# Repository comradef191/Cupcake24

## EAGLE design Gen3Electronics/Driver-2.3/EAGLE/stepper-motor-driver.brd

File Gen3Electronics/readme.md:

# About
The electronics within the final Cupcake24 build will be a modernised variant of the original Gen3 electronics, with the following changes made from the original files:

- PCB & Schematics ported to KiCAD 8.0
  - Reorganisation of Schematic to fit into one small page
  - Symbol locations adjusted to make values easier to read
  - Where possible, Schematic symbols swapped for KiCAD equivalents
  - Where possible, PCB footprints swapped for KiCAD equivalents
- PCB outline re-drawn and rounded-off
- PCB modified to run ground through the groundplane, rather than individual traces
- All traces, text, vias ect adjusted to be entirely metric (I.E: 0.3048mm traces (12mill) changed to 0.3mm traces)
- Silkscreen entirely overhauled, with information more clearly marked, text relocated & re-sized for improved readability, and information about Cupcake24 in an out-of-sight place (Generally, the rear of the PCB, or under a large component such as the SD reader)
- Some minor fixes to some traces not being run entirely in straight lines

# Electronics Status:

**RepRap Motherboard v1.2**
- [x] Converted to modern Eagle
- [x] Files Ported to KiCAD 8.0
- [x] Schematic modernised & cleaned-up
- [ ] PCB Modernised & cleaned-up
- [ ] Component sources designated; BoM Complete
- [ ] PCB Ordered
- [ ] PCB Assembled & Tested
- Comment: PCB mostly complete, some cleanup and tweaks to be done.

**Stepper Motor Driver v2.3**
- [x] Converted to modern Eagle
- [x] Files Ported to KiCAD 8.0
- [x] Schematic modernised & cleaned-up
- [x] PCB Modernised & cleaned-up
- [x] Component sources designated; BoM Complete
- [ ] PCB Ordered
- [ ] PCB Assembled & Tested

**Extruder Controller v2.2**
- [x] Converted to modern Eagle
- [x] Files Ported to KiCAD 8.0
- [ ] Schematic modernised & cleaned-up
- [ ] PCB Modernised & cleaned-up
- [ ] Component sources designated; BoM Complete
- [ ] PCB Ordered
- [ ] PCB Assembled & Tested

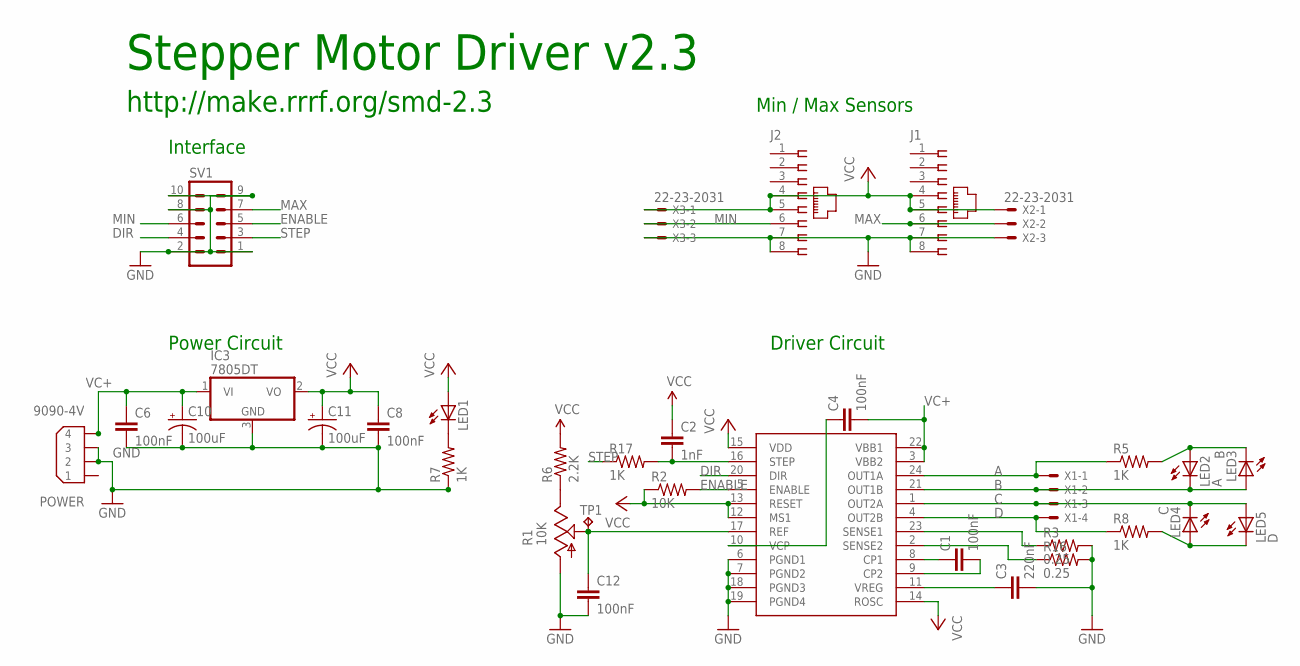
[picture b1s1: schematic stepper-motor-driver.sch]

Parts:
C1, C4, C12: 100nF; C1206
C2: 1nF; C1206K
C3: 220nF; C1206
C6, C8: 100nF; C1206K
C10, C11: 100uF; UD-10X10_NICHICON
DRIVER: A3982; SO24W
IC3: 7805DT; TO252
J1, J2: 520426-4
LED1: LEDCHIPLED_1206; CHIPLED_1206
LED2: A; CHIPLED_1206
LED3: B; CHIPLED_1206
LED4: C; CHIPLED_1206
LED5: D; CHIPLED_1206
POWER: 9090-4V
R1: 10K; B25P
R2: 10K; R1206
R3, R16: 0.25; R2512
R5, R7, R8, R17: 1K; R1206
R6: 2.2K; R1206
SV1: ML10
TP1: TPPAD1-13; P1-13
X1: KK-156-4
X2, X3: 22-23-2031

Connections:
A: DRIVER.24 (OUT1A), R5.1, X1.1
B: DRIVER.21 (OUT1B), LED2.C, LED3.A, X1.2
C: DRIVER.1 (OUT2A), LED4.C, LED5.A, X1.3
D: DRIVER.4 (OUT2B), R8.1, X1.4
DIR: DRIVER.20 (DIR), SV1.4
ENABLE: DRIVER.5 (ENABLE), R2.2, SV1.5
GND: C3.2, C6.2, C8.2, C10.-, C11.-, C12.2, DRIVER.6 (PGND1), DRIVER.7 (PGND2), DRIVER.18 (PGND3), DRIVER.19 (PGND4), IC3.3 (GND), J1.7, J1.8, J2.7, J2.8, POWER.2, POWER.3, R1.A, R3.2, R7.1, R16.2, SV1.1, SV1.2, SV1.8, SV1.9, SV1.10, X2.3, X3.3
MAX: J1.6, SV1.7, X2.2
MIN: J2.6, SV1.6, X3.2
unnamed: DRIVER.23 (SENSE1), R3.1
unnamed: DRIVER.2 (SENSE2), R16.1
unnamed: C1.1, DRIVER.8 (CP1)
unnamed: C1.2, DRIVER.9 (CP2)
unnamed: C3.1, DRIVER.11 (VREG)
unnamed: R1.E, R6.1
unnamed: C4.1, DRIVER.10 (VCP)
unnamed: LED1.C, R7.2
unnamed: LED2.A, LED3.C, R5.2
unnamed: LED4.A, LED5.C, R8.2
unnamed: C12.1, DRIVER.17 (REF), R1.S, TP1.1
unnamed: C2.2, DRIVER.16 (STEP), R17.2
STEP: R17.1, SV1.3
VC+: C4.2, C6.1, C10.+, DRIVER.3 (VBB2), DRIVER.22 (VBB1), IC3.1 (VI), POWER.4
VCC: C2.1, C8.1, C11.+, DRIVER.12 (MS1), DRIVER.13 (RESET), DRIVER.14 (ROSC), DRIVER.15 (VDD), IC3.2 (VO), J1.4, J1.5, J2.4, J2.5, LED1.A, R2.1, R6.2, X2.1, X3.1

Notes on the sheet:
Interface
Driver Circuit
Min / Max Sensors
Stepper Motor Driver v2.3
http://make.rrrf.org/smd-2.3
Power Circuit

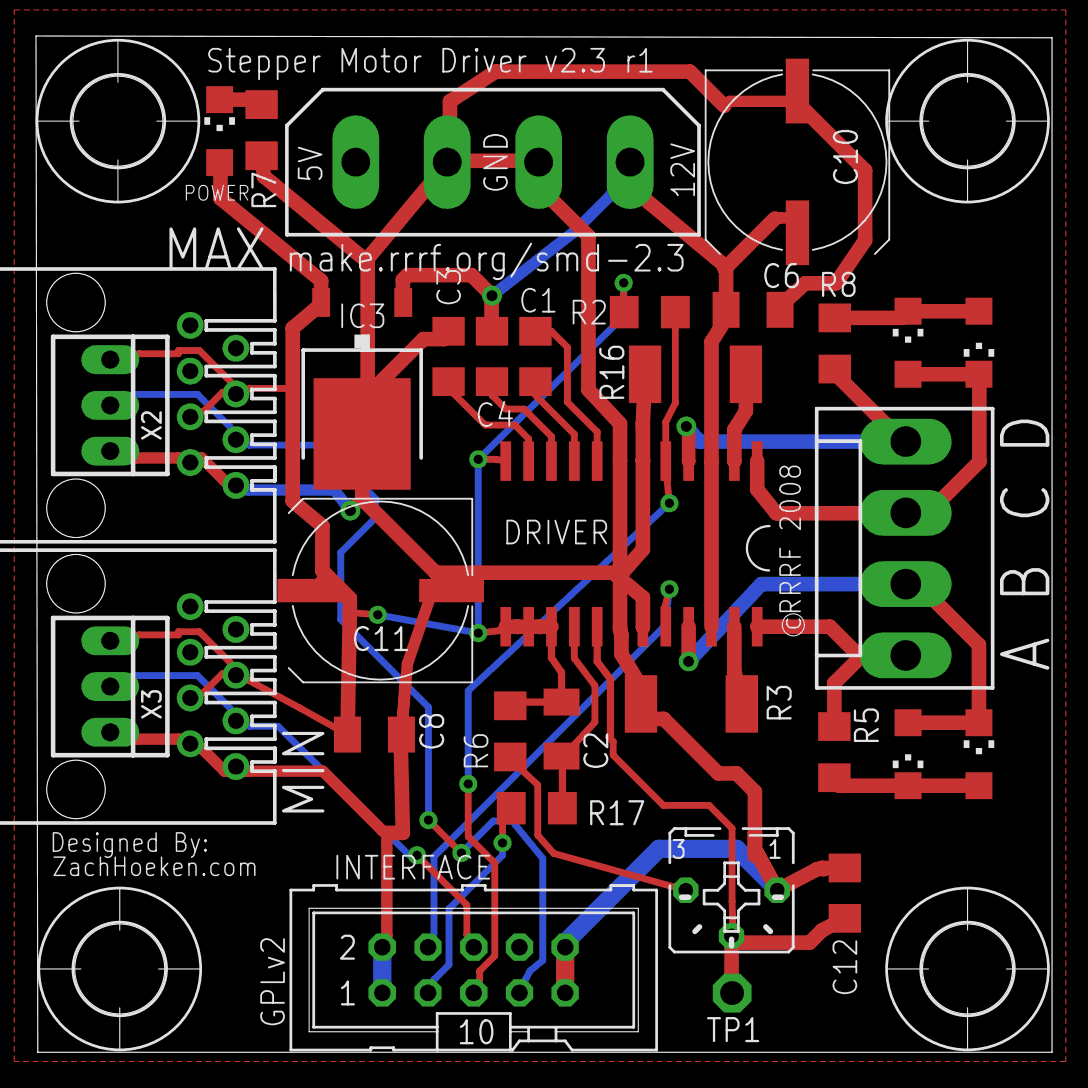
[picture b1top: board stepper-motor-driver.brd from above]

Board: 2 copper layers, 56.4 x 56.5 mm, 37 parts (0 on the bottom side), 24 nets.

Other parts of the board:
U$1, U$2, U$3, U$4: 5,0

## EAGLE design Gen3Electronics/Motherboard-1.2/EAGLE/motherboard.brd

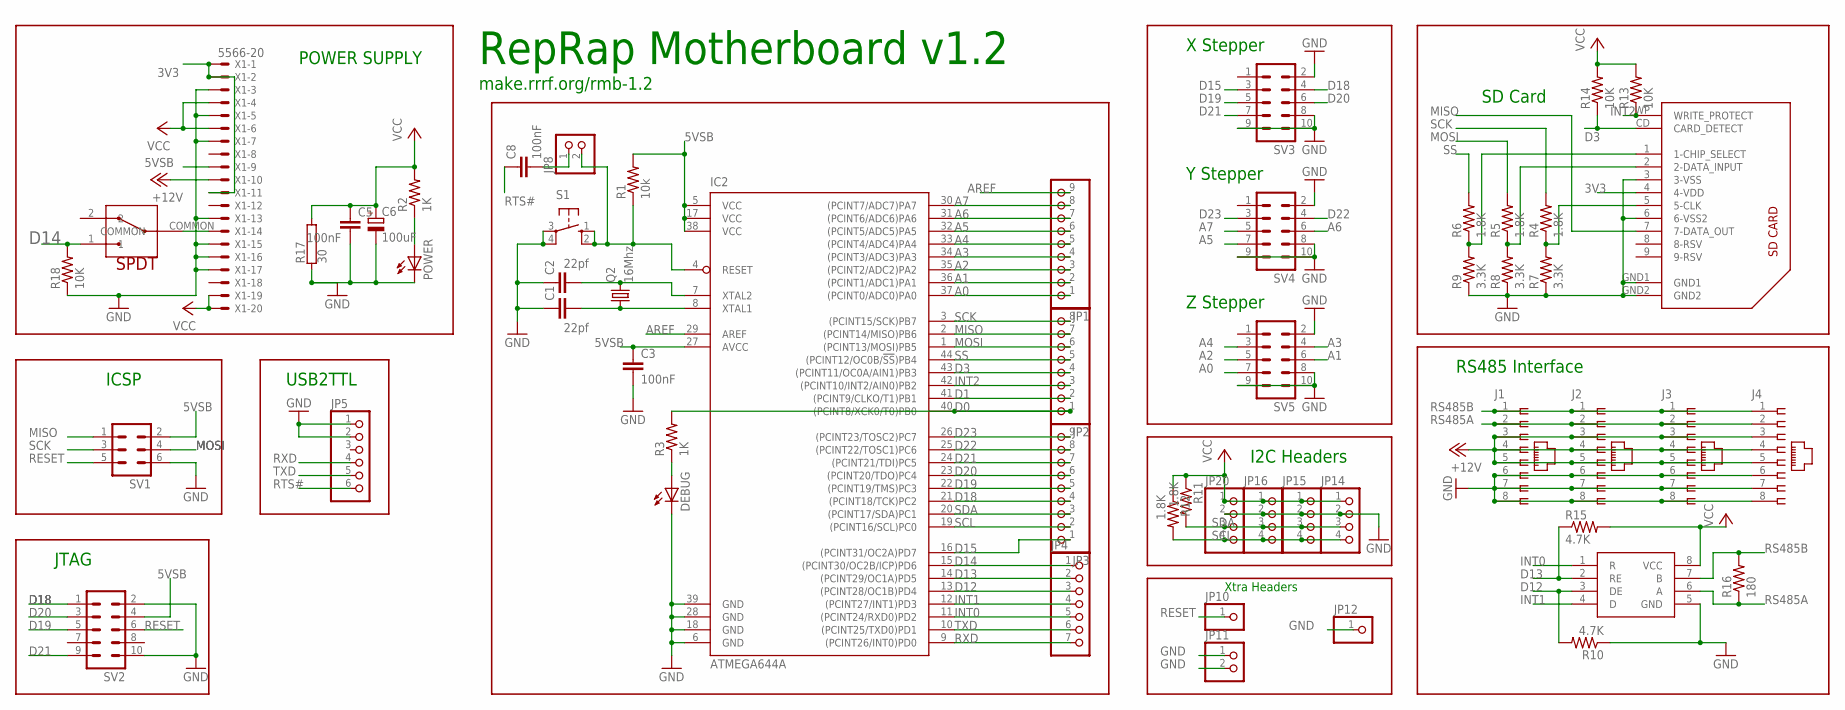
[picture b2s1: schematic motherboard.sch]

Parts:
C1, C2: 22pf; C1206
C3, C5, C8: 100nF; C1206
C6: 100uF; SANYO-OSCON_SMD_B6
DEBUG: LEDCHIPLED_1206; CHIPLED_1206
IC1: SN75176ASOIC; SO08
IC2: ATMEGA644A; TQFP44
J1, J2, J3, J4: 555164-1
JP1, JP3: PINHD-1X9; 1X09
JP2: PINHD-1X8; 1X08
JP4: PINHD-1X7; 1X07
JP5: PINHD-1X6; 1X06
JP8, JP11: PINHD-1X2; 1X02
JP10, JP12: PINHD-1X1; 1X01
JP14, JP15, JP16, JP20: PINHD-1X4; 1X04
POWER: LEDCHIPLED_1206; CHIPLED_1206
Q2: 16Mhz; HC49U-V
R1: 10k; R1206
R2, R3: 1K; R1206
R4, R5, R6, R11, R12: 1.8K; R1206
R7, R8, R9: 3.3K; R1206
R10, R15: 4.7K; R1206
R13, R14, R18: 10K; R1206
R16: 180; R1206
R17: 30; KH206-8
S1: 10-XX; B3F-10XX
SV1: ML6
SV2, SV3, SV4, SV5: ML10
U$2: SPDT; 10SP001
U$8: SDCARD; 3M-SDCARD
X1: 5566-20

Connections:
3V3: U$8.4 (4-VDD), X1.1, X1.2, X1.11
5VSB: C3.1, IC2.5 (VCC), IC2.17 (VCC), IC2.27 (AVCC), IC2.38 (VCC), R1.2, SV1.2, SV2.4, X1.9
+12V: J1.3, J1.4, J1.5, J2.3, J2.4, J2.5, J3.3, J3.4, J3.5, J4.3, J4.4, J4.5, X1.10
A0: IC2.37 ((PCINT0/ADC0)PA0), JP1.1, SV5.7
A1: IC2.36 ((PCINT1/ADC1)PA1), JP1.2, SV5.6
A2: IC2.35 ((PCINT2/ADC2)PA2), JP1.3, SV5.5
A3: IC2.34 ((PCINT3/ADC3)PA3), JP1.4, SV5.4
A4: IC2.33 ((PCINT4/ADC4)PA4), JP1.5, SV5.3
A5: IC2.32 ((PCINT5/ADC5)PA5), JP1.6, SV4.7
A6: IC2.31 ((PCINT6/ADC6)PA6), JP1.7, SV4.6
A7: IC2.30 ((PCINT7/ADC7)PA7), JP1.8, SV4.5
AREF: IC2.29 (AREF), JP1.9
D0: IC2.40 ((PCINT8/XCK0/T0)PB0), JP2.1, R3.2
D1: IC2.41 ((PCINT9/CLKO/T1)PB1), JP2.2
D3: IC2.43 ((PCINT11/OC0A/AIN1)PB3), JP2.4, R14.1, U$8.CD (CARD_DETECT)
D12: IC1.3 (DE), IC2.13 ((PCINT28/OC1B)PD4), JP4.3, R10.2
D13: IC1.2 (RE), IC2.14 ((PCINT29/OC1A)PD5), JP4.2, R15.1
D14: IC2.15 ((PCINT30/OC2B/ICP)PD6), JP4.1, R18.2, U$2.1
D15: IC2.16 ((PCINT31/OC2A)PD7), JP3.1, SV3.3
D18: IC2.21 ((PCINT18/TCK)PC2), JP3.4, SV2.1, SV3.4
D19: IC2.22 ((PCINT19/TMS)PC3), JP3.5, SV2.5, SV3.5
D20: IC2.23 ((PCINT20/TDO)PC4), JP3.6, SV2.3, SV3.6
D21: IC2.24 ((PCINT21/TDI)PC5), JP3.7, SV2.9, SV3.7
D22: IC2.25 ((PCINT22/TOSC1)PC6), JP3.8, SV4.4
D23: IC2.26 ((PCINT23/TOSC2)PC7), JP3.9, SV4.3
GND: C1.1, C2.1, C3.2, C5.2, C6.-, DEBUG.C, IC1.5 (GND), IC2.6 (GND), IC2.18 (GND), IC2.28 (GND), IC2.39 (GND), J1.6, J1.7, J1.8, J2.6, J2.7, J2.8, J3.6, J3.7, J3.8, J4.6, J4.7, J4.8, JP5.1, JP5.2, JP11.1, JP11.2, JP12.1, JP14.2, JP15.2, JP16.2, JP20.2, POWER.C, R7.1, R8.1, R9.1, R10.1, R17.1, R18.1, S1.3, S1.4 (P1), SV1.6, SV2.2, SV2.10, SV3.2, SV3.8, SV3.9, SV3.10, SV4.2, SV4.8, SV4.9, SV4.10, SV5.2, SV5.8, SV5.9, SV5.10, U$8.3 (3-VSS), U$8.6 (6-VSS2), U$8.GND1, U$8.GND2, X1.3, X1.5, X1.7, X1.13, X1.15, X1.16, X1.17
INT0: IC1.1 (R), IC2.11 ((PCINT24/RXD0)PD2), JP4.5
INT1: IC1.4 (D), IC2.12 ((PCINT27/INT1)PD3), JP4.4
INT2: IC2.42 ((PCINT10/INT2/AIN0)PB2), JP2.3, R13.1, U$8.WP (WRITE_PROTECT)
MISO: IC2.2 ((PCINT14/MISO)PB6), JP2.7, SV1.1, U$8.7 (7-DATA_OUT)
MOSI: IC2.1 ((PCINT13/MOSI)PB5), JP2.6, R5.2, SV1.4
unnamed: C2.2, IC2.7 (XTAL2), Q2.2
unnamed: POWER.A, R2.1
unnamed: U$2.COMMON, X1.14
unnamed: DEBUG.A, R3.1
unnamed: C1.2, IC2.8 (XTAL1), Q2.1
unnamed: R6.1, R9.2, U$8.1 (1-CHIP_SELECT)
unnamed: R5.1, R8.2, U$8.2 (2-DATA_INPUT)
unnamed: C8.2, JP8.1
unnamed: R4.1, R7.2, U$8.5 (5-CLK)
RESET: IC2.4 (RESET), JP8.2, JP10.1, R1.1, S1.1 (S), S1.2 (S1), SV1.5, SV2.6
RS485A: IC1.6 (A), J1.2, J2.2, J3.2, J4.2, R16.1
RS485B: IC1.7 (B), J1.1, J2.1, J3.1, J4.1, R16.2
RTS#: C8.1, JP5.6
RXD: IC2.9 ((PCINT26/INT0)PD0), JP4.7, JP5.4
SCK: IC2.3 ((PCINT15/SCK)PB7), JP2.8, R4.2, SV1.3
SCL: IC2.19 ((PCINT16/SCL)PC0), JP3.2, JP14.4, JP15.4, JP16.4, JP20.4, R12.2
SDA: IC2.20 ((PCINT17/SDA)PC1), JP3.3, JP14.3, JP15.3, JP16.3, JP20.3, R11.2
SS: IC2.44 ((PCINT12/OC0B/!SS!)PB4), JP2.5, R6.2
TXD: IC2.10 ((PCINT25/TXD0)PD1), JP4.6, JP5.5
VCC: C5.1, C6.+, IC1.8 (VCC), JP14.1, JP15.1, JP16.1, JP20.1, R2.2, R11.1, R12.1, R13.2, R14.2, R15.2, R17.2, X1.4, X1.6, X1.19, X1.20

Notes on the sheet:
ICSP
USB2TTL
POWER SUPPLY
RepRap Motherboard v1.2
make.rrrf.org/rmb-1.2
JTAG
Xtra Headers
Z Stepper
Y Stepper
X Stepper
SD Card
I2C Headers
RS485 Interface

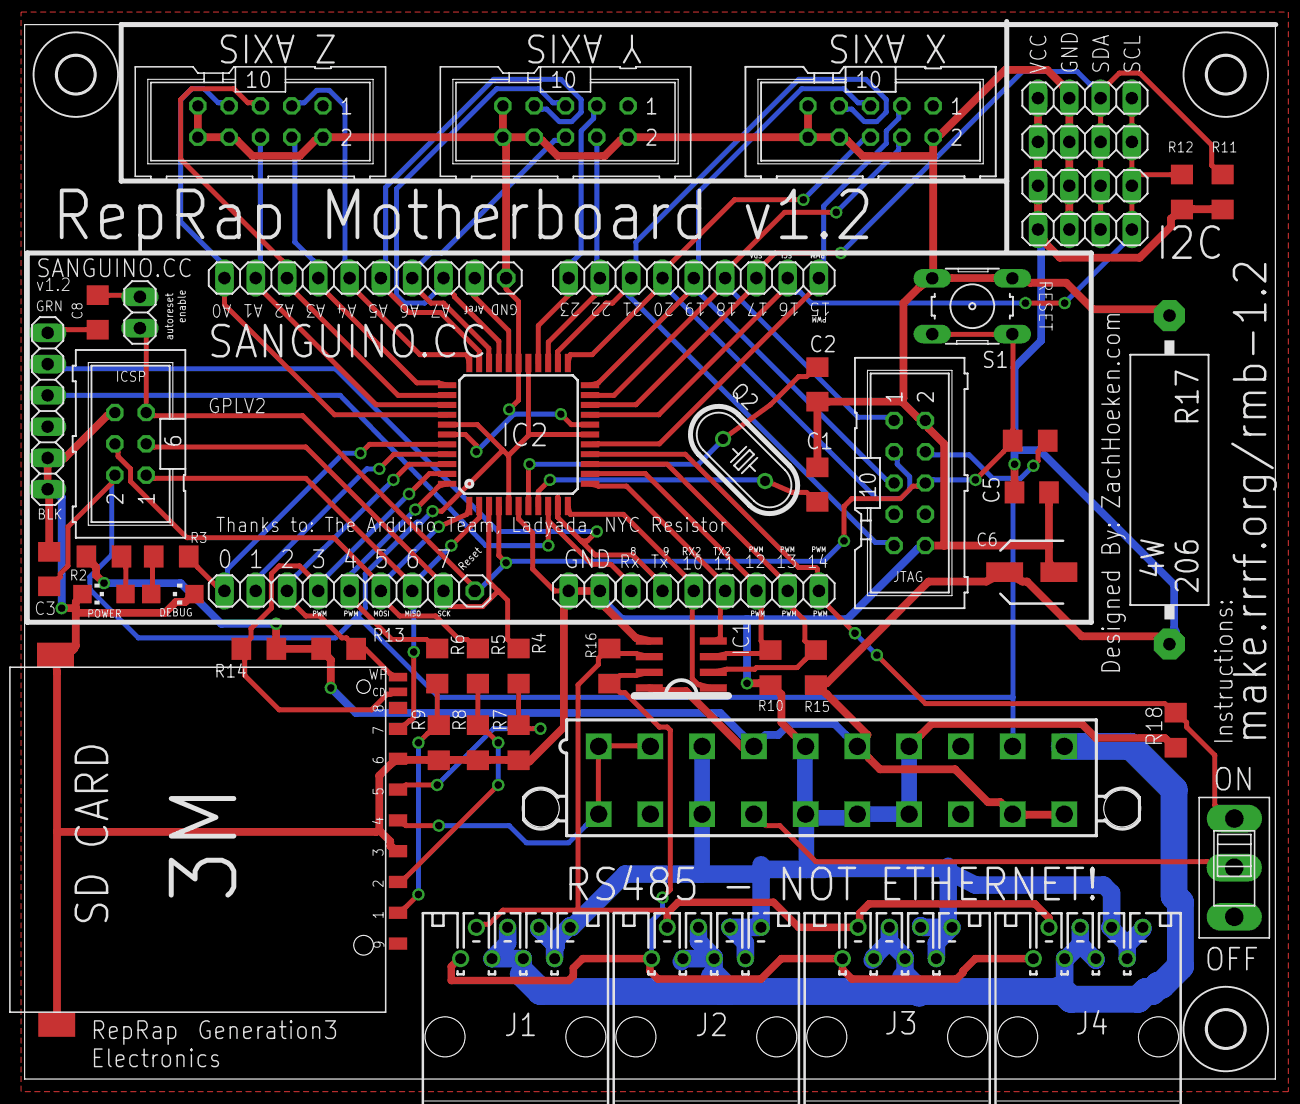
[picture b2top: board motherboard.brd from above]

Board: 2 copper layers, 101.5 x 85.6 mm, 58 parts (0 on the bottom side), 51 nets.

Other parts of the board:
U$3, U$4, U$5: 3,0

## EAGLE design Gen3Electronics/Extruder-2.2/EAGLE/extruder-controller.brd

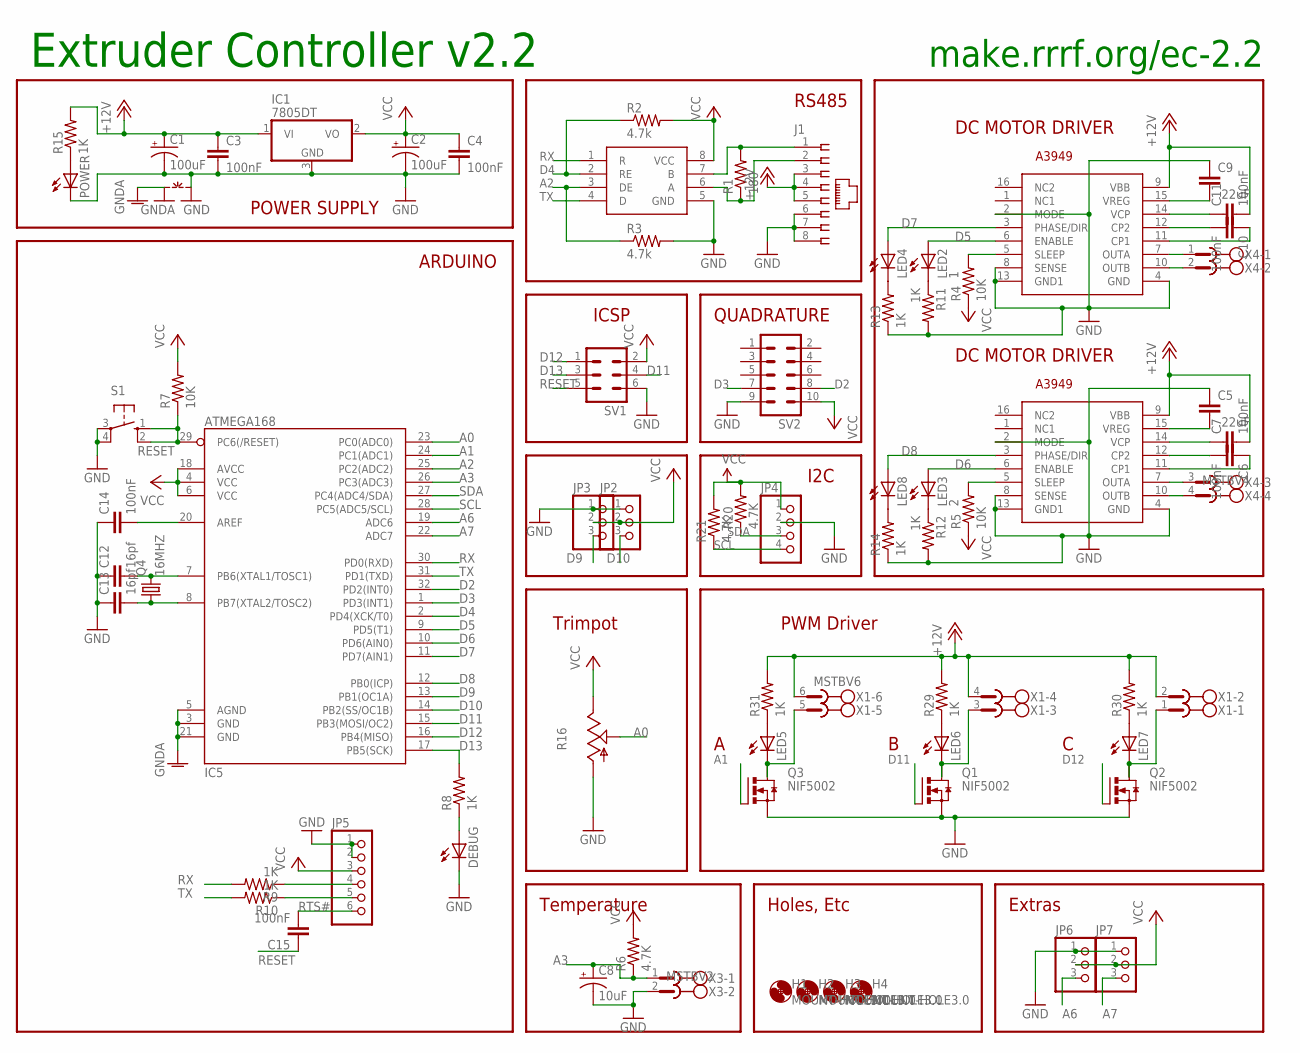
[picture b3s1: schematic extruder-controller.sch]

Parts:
C1, C2: 100uF; UD-10X10_NICHICON
C3, C4, C14, C15: 100nF; C1206
C5, C9: .22uF; C1206K
C6, C7, C10, C11: 100nF; C1206K
C8: 10uF; UD-6,3X5,8_NICHICON
C12, C13: 16pf; C1206
DEBUG: LEDCHIPLED_1206; CHIPLED_1206
H1, H2, H3, H4: MOUNT-HOLE3.0; 3,0
IC1: 7805DT; TO252
IC2, IC3: A3949; SO16W
IC4: SN75176ASOIC; SO08
IC5: ATMEGA168; TQFP32-08
J1: 520426-4
JP2, JP3, JP6, JP7: PINHD-1X3; 1X03
JP4: PINHD-1X4; 1X04
JP5: PINHD-1X6; 1X06
LED2: 1; CHIPLED_1206
LED3: 2; CHIPLED_1206
LED4, LED5, LED6, LED7, LED8: LEDCHIPLED_1206; CHIPLED_1206
POWER: LEDCHIPLED_1206; CHIPLED_1206
Q1, Q2, Q3: NIF5002; SOT223
Q4: 16MHZ; HC49/S
R1: 180; R1206
R2, R3: 4.7k; R1206
R4, R5, R7: 10K; R1206
R6: 4.7K; M1206
R8, R9, R10, R11, R12, R13, R14, R15, R29, R30: 1K; R1206
R16: TRIM_US-B25P; B25P
R20, R21: 4.7K; R1206
R31: 1K; M1206
S1: 10-XX; B3F-10XX
SV1: ML6
SV2: ML10
X1: MSTBV6
X3: MSTBV2
X4: MSTBV4
~NUDEV~1: GND-GNDA

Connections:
+12V: C1.+, C3.1, C7.2, C11.2, IC1.1 (VI), IC2.9 (VBB), IC3.9 (VBB), J1.3, J1.4, J1.5, R15.2, R29.2, R30.2, R31.2, X1.2, X1.4, X1.6
A0: IC5.23 (PC0(ADC0)), R16.S
A1: IC5.24 (PC1(ADC1)), Q3.1 (G)
A2: IC4.3 (DE), IC5.25 (PC2(ADC2)), R3.1
A3: C8.+, IC5.26 (PC3(ADC3)), R6.1, X3.1
A6: IC5.19 (ADC6), JP6.3
A7: IC5.22 (ADC7), JP7.3
D2: IC5.32 (PD2(INT0)), SV2.8
D3: IC5.1 (PD3(INT1)), SV2.7
D4: IC4.2 (RE), IC5.2 (PD4(XCK/T0)), R2.1
D5: IC2.6 (ENABLE), IC5.9 (PD5(T1)), LED2.A
D6: IC3.6 (ENABLE), IC5.10 (PD6(AIN0)), LED3.A
D7: IC2.3 (PHASE/DIR), IC5.11 (PD7(AIN1)), LED4.A
D8: IC3.3 (PHASE/DIR), IC5.12 (PB0(ICP)), LED8.A
D9: IC5.13 (PB1(OC1A)), JP3.3
D10: IC5.14 (PB2(SS/OC1B)), JP2.3
D11: IC5.15 (PB3(MOSI/OC2)), Q1.1 (G), SV1.4
D12: IC5.16 (PB4(MISO)), Q2.1 (G), SV1.1
D13: IC5.17 (PB5(SCK)), R8.2, SV1.3
GND: C1.-, C2.-, C3.2, C4.2, C5.1, C8.-, C9.1, C12.1, C13.1, C14.1, DEBUG.C, IC1.3 (GND), IC2.2 (MODE), IC2.4 (GND), IC2.8 (SENSE), IC2.13 (GND1), IC3.2 (MODE), IC3.4 (GND), IC3.8 (SENSE), IC3.13 (GND1), IC4.5 (GND), J1.6, J1.7, J1.8, JP2.1, JP3.1, JP4.2, JP5.1, JP5.2, JP6.1, JP7.1, POWER.C, Q1.3 (S), Q2.3 (S), Q3.3 (S), R3.2, R11.2, R12.2, R13.1, R14.1, R16.A, S1.3, S1.4 (P1), SV1.6, SV2.9, X3.2, ~NUDEV~1.GND
GNDA: IC5.3 (GND), IC5.5 (AGND), IC5.21 (GND), ~NUDEV~1.GNDA
unnamed: IC4.7 (B), J1.1, R1.2
unnamed: IC4.6 (A), J1.2, R1.1
unnamed: C9.2, IC2.15 (VREG)
unnamed: IC2.7 (OUTA), X4.1
unnamed: IC2.10 (OUTB), X4.2
unnamed: C10.2, IC2.12 (CP2)
unnamed: C10.1, IC2.11 (CP1)
unnamed: DEBUG.A, R8.1
unnamed: C11.1, IC2.14 (VCP)
unnamed: IC3.7 (OUTA), X4.3
unnamed: C5.2, IC3.15 (VREG)
unnamed: IC2.5 (SLEEP), R4.2
unnamed: C6.2, IC3.12 (CP2)
unnamed: C6.1, IC3.11 (CP1)
unnamed: C7.1, IC3.14 (VCP)
unnamed: IC3.5 (SLEEP), R5.2
unnamed: IC3.10 (OUTB), X4.4
unnamed: LED2.C, R11.1
unnamed: LED3.C, R12.1
unnamed: C14.2, IC5.20 (AREF)
unnamed: JP5.5, R10.1
unnamed: JP5.4, R9.1
unnamed: LED4.C, R13.2
unnamed: LED8.C, R14.2
unnamed: POWER.A, R15.1
unnamed: C12.2, IC5.7 (PB6(XTAL1/TOSC1)), Q4.2
unnamed: C13.2, IC5.8 (PB7(XTAL2/TOSC2)), Q4.1
unnamed: LED7.C, Q2.2 (D), Q2.4 (D), X1.1
unnamed: LED6.C, Q1.2 (D), Q1.4 (D), X1.3
unnamed: LED5.C, Q3.2 (D), Q3.4 (D), X1.5
unnamed: LED5.A, R31.1
unnamed: LED6.A, R29.1
unnamed: LED7.A, R30.1
RESET: C15.1, IC5.29 (PC6(/RESET)), R7.1, S1.1 (S), S1.2 (S1), SV1.5
RTS#: C15.2, JP5.6
RX: IC4.1 (R), IC5.30 (PD0(RXD)), R9.2
SCL: IC5.28 (PC5(ADC5/SCL)), JP4.4, R21.1
SDA: IC5.27 (PC4(ADC4/SDA)), JP4.3, R20.1
TX: IC4.4 (D), IC5.31 (PD1(TXD)), R10.2
VCC: C2.+, C4.1, IC1.2 (VO), IC4.8 (VCC), IC5.4 (VCC), IC5.6 (VCC), IC5.18 (AVCC), JP2.2, JP3.2, JP4.1, JP5.3, JP6.2, JP7.2, R2.2, R4.1, R5.1, R6.2, R7.2, R16.E, R20.2, R21.2, SV1.2, SV2.10

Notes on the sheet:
Extruder Controller v2.2
POWER SUPPLY
RS485
QUADRATURE
I2C
DC MOTOR DRIVER
PWM Driver
Temperature
ICSP
ARDUINO
Extras
Holes, Etc
make.rrrf.org/ec-2.2
Trimpot

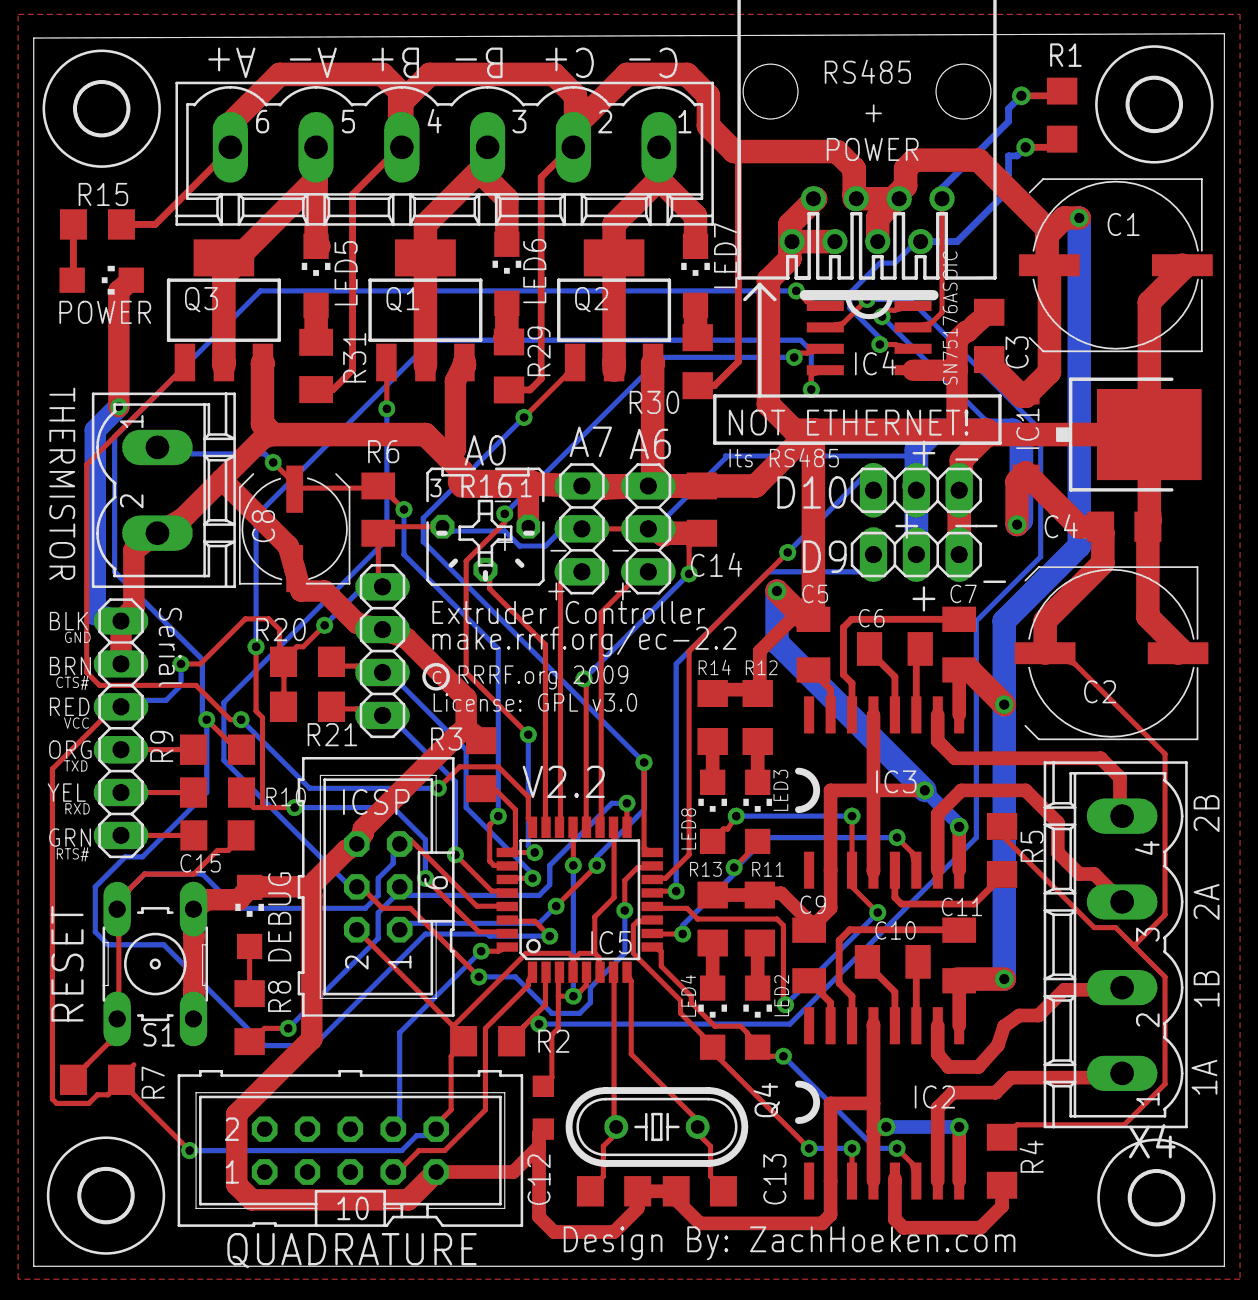
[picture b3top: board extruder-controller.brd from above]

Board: 2 copper layers, 70.5 x 73.0 mm, 72 parts (0 on the bottom side), 61 nets.

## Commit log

2024-11-07 Add all current files for the Electronics

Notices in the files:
Gen3Electronics/Driver-2.3/EAGLE/stepper-motor-driver.brd:
GPLv2
Gen3Electronics/Extruder-2.2/EAGLE/extruder-controller.brd:
License: GPL v3.0
